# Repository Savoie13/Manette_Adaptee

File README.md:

# Manette Adaptée : Jouer sans limite
## Mathis Savoie et Jackob Breton
Ce répertoire GitHub est pour le projet de manette adapté avec l’école du Touret. Nous sommes 2 finissants en technologie de systèmes ordinés et le projet que nous allons tenter de réaliser est de programmer un Arduino Micro pour faire une manette pour des jeux Scratch. Cette manette adaptée permettra aux élèves de l’école du Touret qui ont moins de mobilité de jouer à des jeux vidéo comme leurs camarades. La manette sera composée de gros boutons et joysticks et permettra de brancher divers boutons pour plus de fonctionnalités. La manette comporte aussi un ESP8266 afin de pouvoir, grâce à une interface d’usager WEB, configurer la manette et ses boutons.

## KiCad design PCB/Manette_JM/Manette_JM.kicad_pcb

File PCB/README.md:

# PCB
Ce dossier contient les schémas et PCBs de la manette adaptée

Le répertoire Manette_JM contient le projet KiCad

Le répertoire Manette_JM_Gerber contient les fichiers Gerber afin de l'envoyer à une compagie de fabrication de PCB.

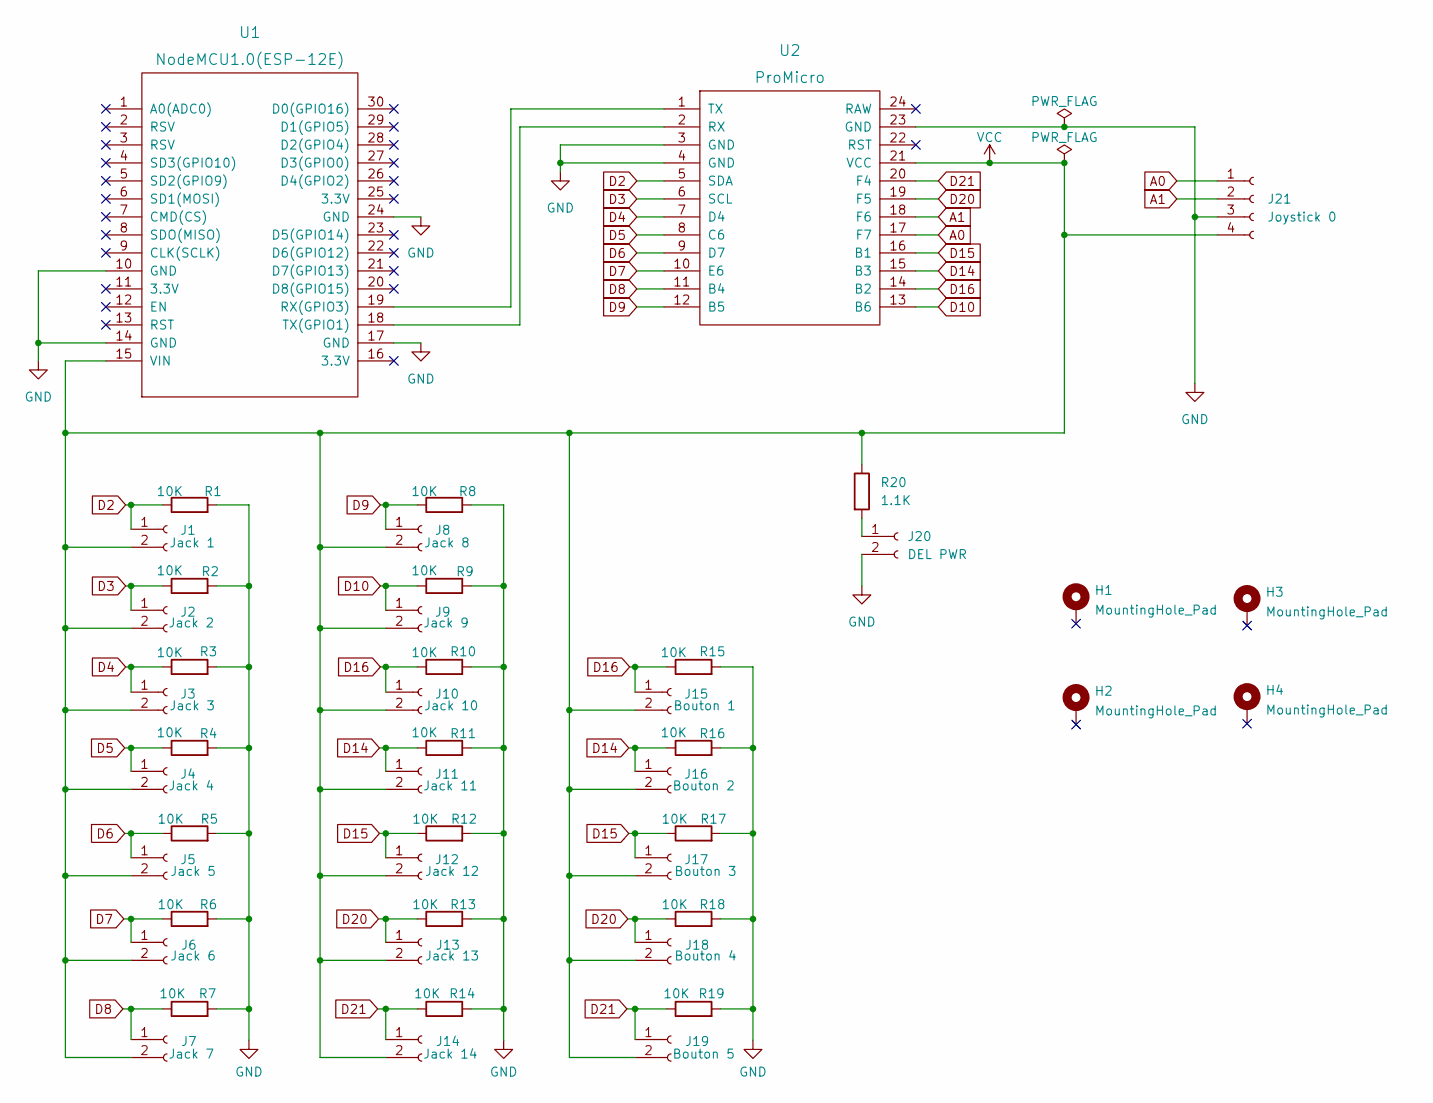
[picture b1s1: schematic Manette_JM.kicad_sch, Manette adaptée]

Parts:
H1, H2, H3, H4: MountingHole_Pad; MountingHole_3.2mm_M3_Pad_Via
J1: Jack 1; PinHeader_1x02_P2.54mm_Vertical
J2: Jack 2; PinHeader_1x02_P2.54mm_Vertical
J3: Jack 3; PinHeader_1x02_P2.54mm_Vertical
J4: Jack 4; PinHeader_1x02_P2.54mm_Vertical
J5: Jack 5; PinHeader_1x02_P2.54mm_Vertical
J6: Jack 6; PinHeader_1x02_P2.54mm_Vertical
J7: Jack 7; PinHeader_1x02_P2.54mm_Vertical
J8: Jack 8; PinHeader_1x02_P2.54mm_Vertical
J9: Jack 9; PinHeader_1x02_P2.54mm_Vertical
J10: Jack 10; PinHeader_1x02_P2.54mm_Vertical
J11: Jack 11; PinHeader_1x02_P2.54mm_Vertical
J12: Jack 12; PinHeader_1x02_P2.54mm_Vertical
J13: Jack 13; PinHeader_1x02_P2.54mm_Vertical
J14: Jack 14; PinHeader_1x02_P2.54mm_Vertical
J15: Bouton 1; PinHeader_1x02_P2.54mm_Vertical
J16: Bouton 2; PinHeader_1x02_P2.54mm_Vertical
J17: Bouton 3; PinHeader_1x02_P2.54mm_Vertical
J18: Bouton 4; PinHeader_1x02_P2.54mm_Vertical
J19: Bouton 5; PinHeader_1x02_P2.54mm_Vertical
J20: DEL PWR; PinHeader_1x02_P2.54mm_Vertical
J21: Joystick 0; PinHeader_1x04_P2.54mm_Vertical
R1, R2, R3, R4, R5, R6, R7, R8, R9, R10, R11, R12, R13, R14, R15, R16, R17, R18, R19: 10K; R_0805_2012Metric_Pad1.20x1.40mm_HandSolder
R20: 1.1K; R_0805_2012Metric_Pad1.20x1.40mm_HandSolder
U1: NodeMCU1.0(ESP-12E); NodeMCU-LoLinV3
U2: ProMicro

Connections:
A0: J21.1, U2.17 (F7)
A1: J21.2, U2.18 (F6)
D2: J1.1, R1.1, U2.5 (SDA)
D3: J2.1, R2.1, U2.6 (SCL)
D4: J3.1, R3.1, U2.7 (D4)
D5: J4.1, R4.1, U2.8 (C6)
D6: J5.1, R5.1, U2.9 (D7)
D7: J6.1, R6.1, U2.10 (E6)
D8: J7.1, R7.1, U2.11 (B4)
D9: J8.1, R8.1, U2.12 (B5)
D10: J9.1, R9.1, U2.13 (B6)
D14: J11.1, J16.1, R11.1, R16.1, U2.15 (B3)
D15: J12.1, J17.1, R12.1, R17.1, U2.16 (B1)
D16: J10.1, J15.1, R10.1, R15.1, U2.14 (B2)
D20: J13.1, J18.1, R13.1, R18.1, U2.19 (F5)
D21: J14.1, J19.1, R14.1, R19.1, U2.20 (F4)
GND: J20.2, J21.3, R1.2, R2.2, R3.2, R4.2, R5.2, R6.2, R7.2, R8.2, R9.2, R10.2, R11.2, R12.2, R13.2, R14.2, R15.2, R16.2, R17.2, R18.2, R19.2, U1.10 (GND), U1.14 (GND), U1.17 (GND), U1.24 (GND), U2.3 (GND), U2.4 (GND), U2.23 (GND)
unnamed: J20.1, R20.2
unnamed: U1.18 (TX(GPIO1)), U2.2 (RX)
unnamed: U1.19 (RX(GPIO3)), U2.1 (TX)
VCC: J1.2, J2.2, J3.2, J4.2, J5.2, J6.2, J7.2, J8.2, J9.2, J10.2, J11.2, J12.2, J13.2, J14.2, J15.2, J16.2, J17.2, J18.2, J19.2, J21.4, R20.1, U1.15 (VIN), U2.21 (VCC)

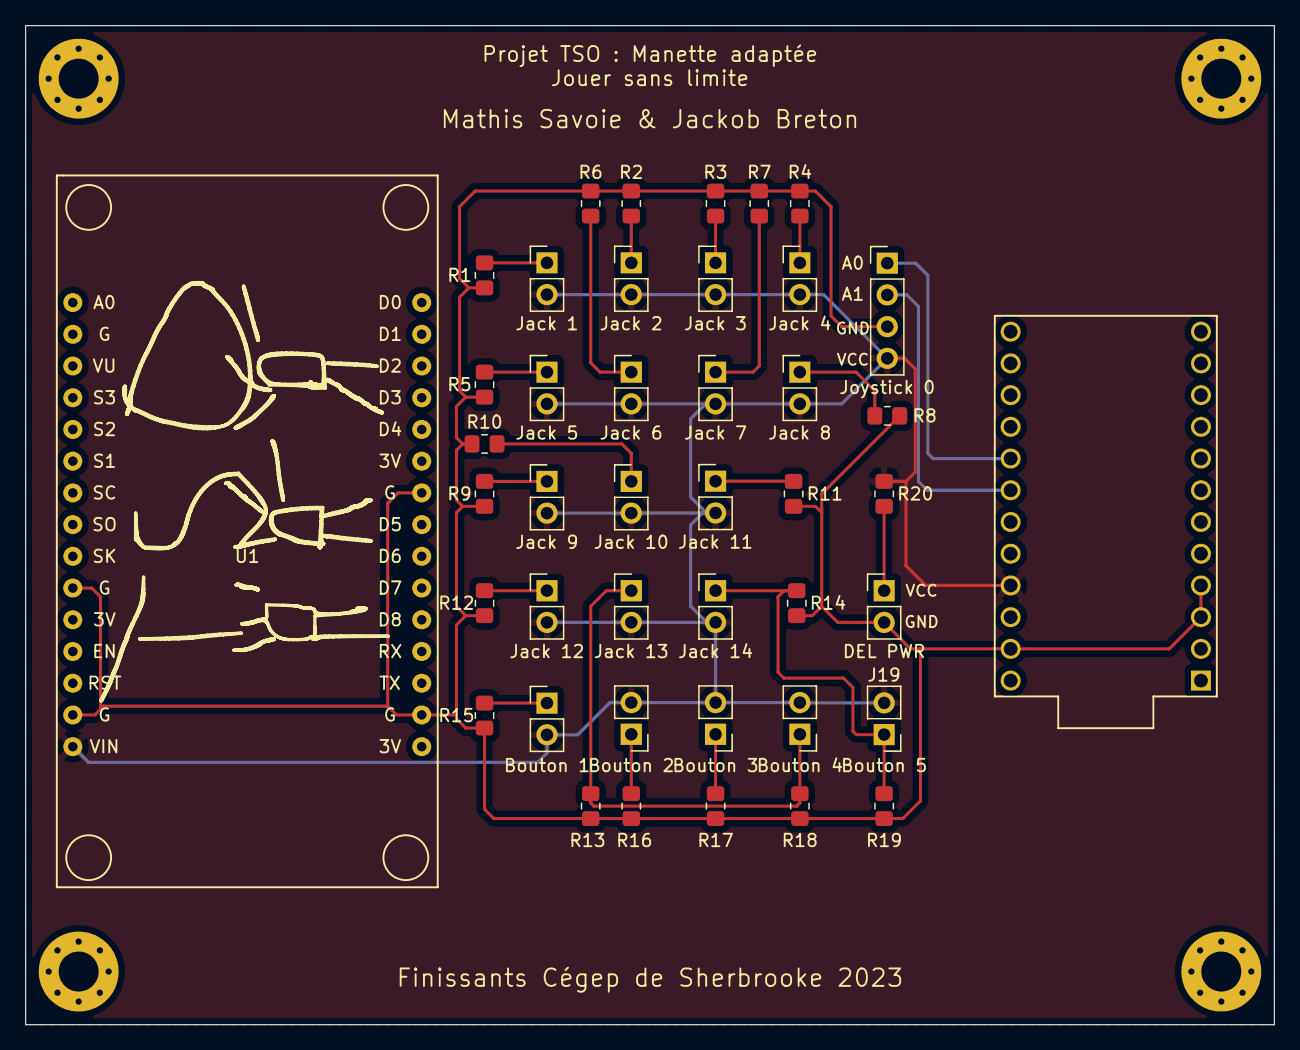
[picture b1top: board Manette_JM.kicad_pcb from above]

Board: 4 copper layers, 100.0 x 80.0 mm, 47 parts (0 on the bottom side), 21 nets.

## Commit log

2023-01-19 Create Logo
2023-01-19 Revert "Create Logo"
    This reverts commit 7ae190462524e206dc402f4146201618d5ce083e.
2023-01-19 First prog commit
2023-01-19 Rename README.md.txt to README.md
2023-01-19 commit new folders
2023-01-19 commit 3d changes
2023-01-19 Add docu
2023-01-19 quick changes
2023-01-23 docx add
2023-01-23 rename_presentation
2023-01-24 KiCad V1 Manette
2023-01-26 rename_affiche
2023-01-26 rename presentation
2023-01-26 Schéma électrique et début PCB
2023-01-31 Quick changes
    modification code et schéma
2023-01-31 PCB upgrade
2023-02-03 PCB changes
2023-02-06 Create Pieces_commande.xlsx
    Pièces à commander
2023-02-06 quick chanfes
2023-02-06 quick pcb changes
2023-02-09 Website
2023-02-09 Prog changes
2023-02-13 update esp
2023-02-13 New Controller version
2023-02-14 liste boutons et update site web
2023-02-20 Prog update
2023-02-20 Quick PCB change
    corrigé une faute d'orthographe
2023-02-20 Update Full_controllerV4.ino
    finis les commentaires du programme
2023-02-21 okok
2023-03-06 ESP_WEB
2023-03-16 quick change
2023-03-20 quick manu change
2023-03-22 Create Full_controllerV5.ino
    Newer and more optimized version of my code Full_controllerV4
2023-03-23 Create QrCode.pptx
    Qr Code Update
2023-03-27 Version plus propre du répertoire de l'ESP8266
    Beaucoup de changement dans le répertoire. J'ai ajouté les nouveaux fichiers et j'ai retiré les anciens. J'ai aussi ajouter des read.me
2023-03-27 update
    j'ai commenté le code de Full_controllerV5 et j'ai avancé le manuel technique
2023-03-27 Ajout d'un README.md
    Commentaires ajoutés afin de faciliter la compréhension.
2023-03-27 Ajout de Read.me dans les dossier de programmation
2023-03-28 reorder
    replacé les fichiers du dossier de programmatiion
2023-03-28 Create README.md
    Ajout du read.me dans le code Full_controllerV5
2023-04-11 Update manuel_technique_manette_adaptée.docx
    J'ai mis la dernière version du manuel technique sur le Git
2023-04-11 Update WriteEEPROM.ino
    Commented WriteEEPROM.ino and added a BRIEF
2023-04-11 Update Full_controllerV5.ino
    Commented Full_controllerV5.ino
2023-04-11 Update WriteEEPROM.ino
    Commented WriteEEPROM.ino
2023-04-11 Update Full_controllerV5.ino
    Finished comments on Full_controllerV5.ino
2023-04-20 Ajout du code commenté
2023-04-20 ajout du nouveau joystick
    Manche de joystick pour le nouveau joystick que nous avons installé
2023-04-25 Code ESP
    Code complété pour l'ESP8266.
2023-04-25 changements rapides des codes
2023-04-27 Update Full_controllerV5.ino
    J'ai ajouté une ligne que j'avais oublié
2023-05-01 Changement code ESP
    Nous avons ajouté la nouvelle façon de programmer l'ESP8266 et nous avons mis l'ancienne version dans "old versions"
2023-05-01 modif readme.md
2023-05-01 Commentaire
    Code commenté
2023-05-02 update documentation
2023-05-02 update docu
2023-05-04 modification sur le site web
2023-05-04 Nettoyage et changement
    Changement de descriptions et de fichiers. Le GitHub est maintenant plus propre.
2023-05-05 nouvelle version manuel technique
2023-05-09 quelques modifications pour le style
    style de la page web
